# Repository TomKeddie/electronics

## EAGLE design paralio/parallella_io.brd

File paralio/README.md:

# Parallella IO motherboard

# Rev 1.1

## IO Mapping

| Linux GPIO | Zynq Pin | PEC PIN | PEC NAME | Arduino Pin | Local Function |
| ---------- | -------- | ------- | -------- | ----------- | -------------- |

## Issues list
- DFM, need to remove components from underside to reduce cost

# Rev 1.0
## IO Mapping (to be verified)
| Linux GPIO | Zynq Pin | Zynq Name | PEC PIN | PEC NAME | Arduino Pin | Local Function |
| ---- | ---- | ---- | ---- | ---- | ---- | ---- |
| 54 | U17 | IO_L9N_T1_DQS_34             | F3 | GPIO0_N | D7 | - |
| 56 | T16 | IO_L9P_T1_DQS_34             | F5 | GPIO0_P | D6 | -  |
| 1 | W16 | IO_L18N_T2_34                | F4 | GPIO1_N | A0 | LCD_D0 |
| 3 | V16 | IO_L18P_T2_34                | F6 | GPIO1_P | A1 | LCD_D1 |
| 58 | P16 | IO_L24N_T3_34                    | F7 | GPIO2_N | D5 | - |
| 60 | P15 | IO_L24P_T3_34                    | F9 | GPIO2_P | D4 | - |
| 5 | U19 | IO_L12P_T1_MRCC_34               | F8 | GPIO3_N | A2 | LCD_D2 |
| 7 | U18 | IO_L12N_T1_MRCC_34               | F10 | GPIO3_P | A3 | LCD_D3 |
| 62 | R14 | IO_L6N_T0_VREF_34                | F13 | GPIO4_N | D3 | - |
| 64 | P14 | IO_L6P_T0_34                     | F15 | GPIO4_P | D2 | - |
| 9 | T15 | IO_L5N_T0_34                     | F14 | GPIO5_N | A4 | LCD_D4 |
| 11 | T14 | IO_L5P_T0_34                       | F16 | GPIO5_P | A5 | LCD_D5 |
| 66 | U15 | IO_L11N_T1_SRCC_34             | F17 | GPIO6_N | D1/TX | - |
| 68 | U14 | IO_L11P_T1_SRCC_34             | F19 | GPIO6_P | D0/RX | - |
| 13 | W14 | IO_L8N_T1_34                   | F18 | GPIO7_N | - | LCD_D6 |
| 15 | Y14 | IO_L8P_T1_34                   | F20 | GPIO7_P | - | LCD_D7 |
| 16 | V13 | IO_L3N_T0_DQS_34                   | F23 | GPIO8_N | D11 | - |
| 18 | U13 | IO_L3P_T0_DQS_PUDC_B_34 | F25 | GPIO8_P | D10 | LCD_E |
| 17 | W12 | IO_L4N_T0_34            | F24 | GPIO9_N | SDA* | - |
| 19 | V13 | IO_L4P_T0_34             | F26 | GPIO9_P | SCL* | - |
| 20 | U12 | IO_L2N_T0_34             | F27 | GPIO10_N | D9 | LCD_RW |
| 22 | T12 | IO_L2P_T0_34             | F29 | GPIO10_P | D8 | LCD_RS  |
| 21 | T10 | IO_L1N_T0_34             | F28 | GPIO11_N | D13 | - |
| 23 | T11 | IO_L1P_T0_34             | F30 | GPIO11_P | D12 | - |

## Issues list

- Random large vias
- Buttons on same i/o as lcd
- I2C not bidirectional
- wrong package on ULN2803
- connector on parallela hits the led uln2803
- cap beside xilinx jtag clashes with cap on parallela
- shunt and fan connector block access to microsd

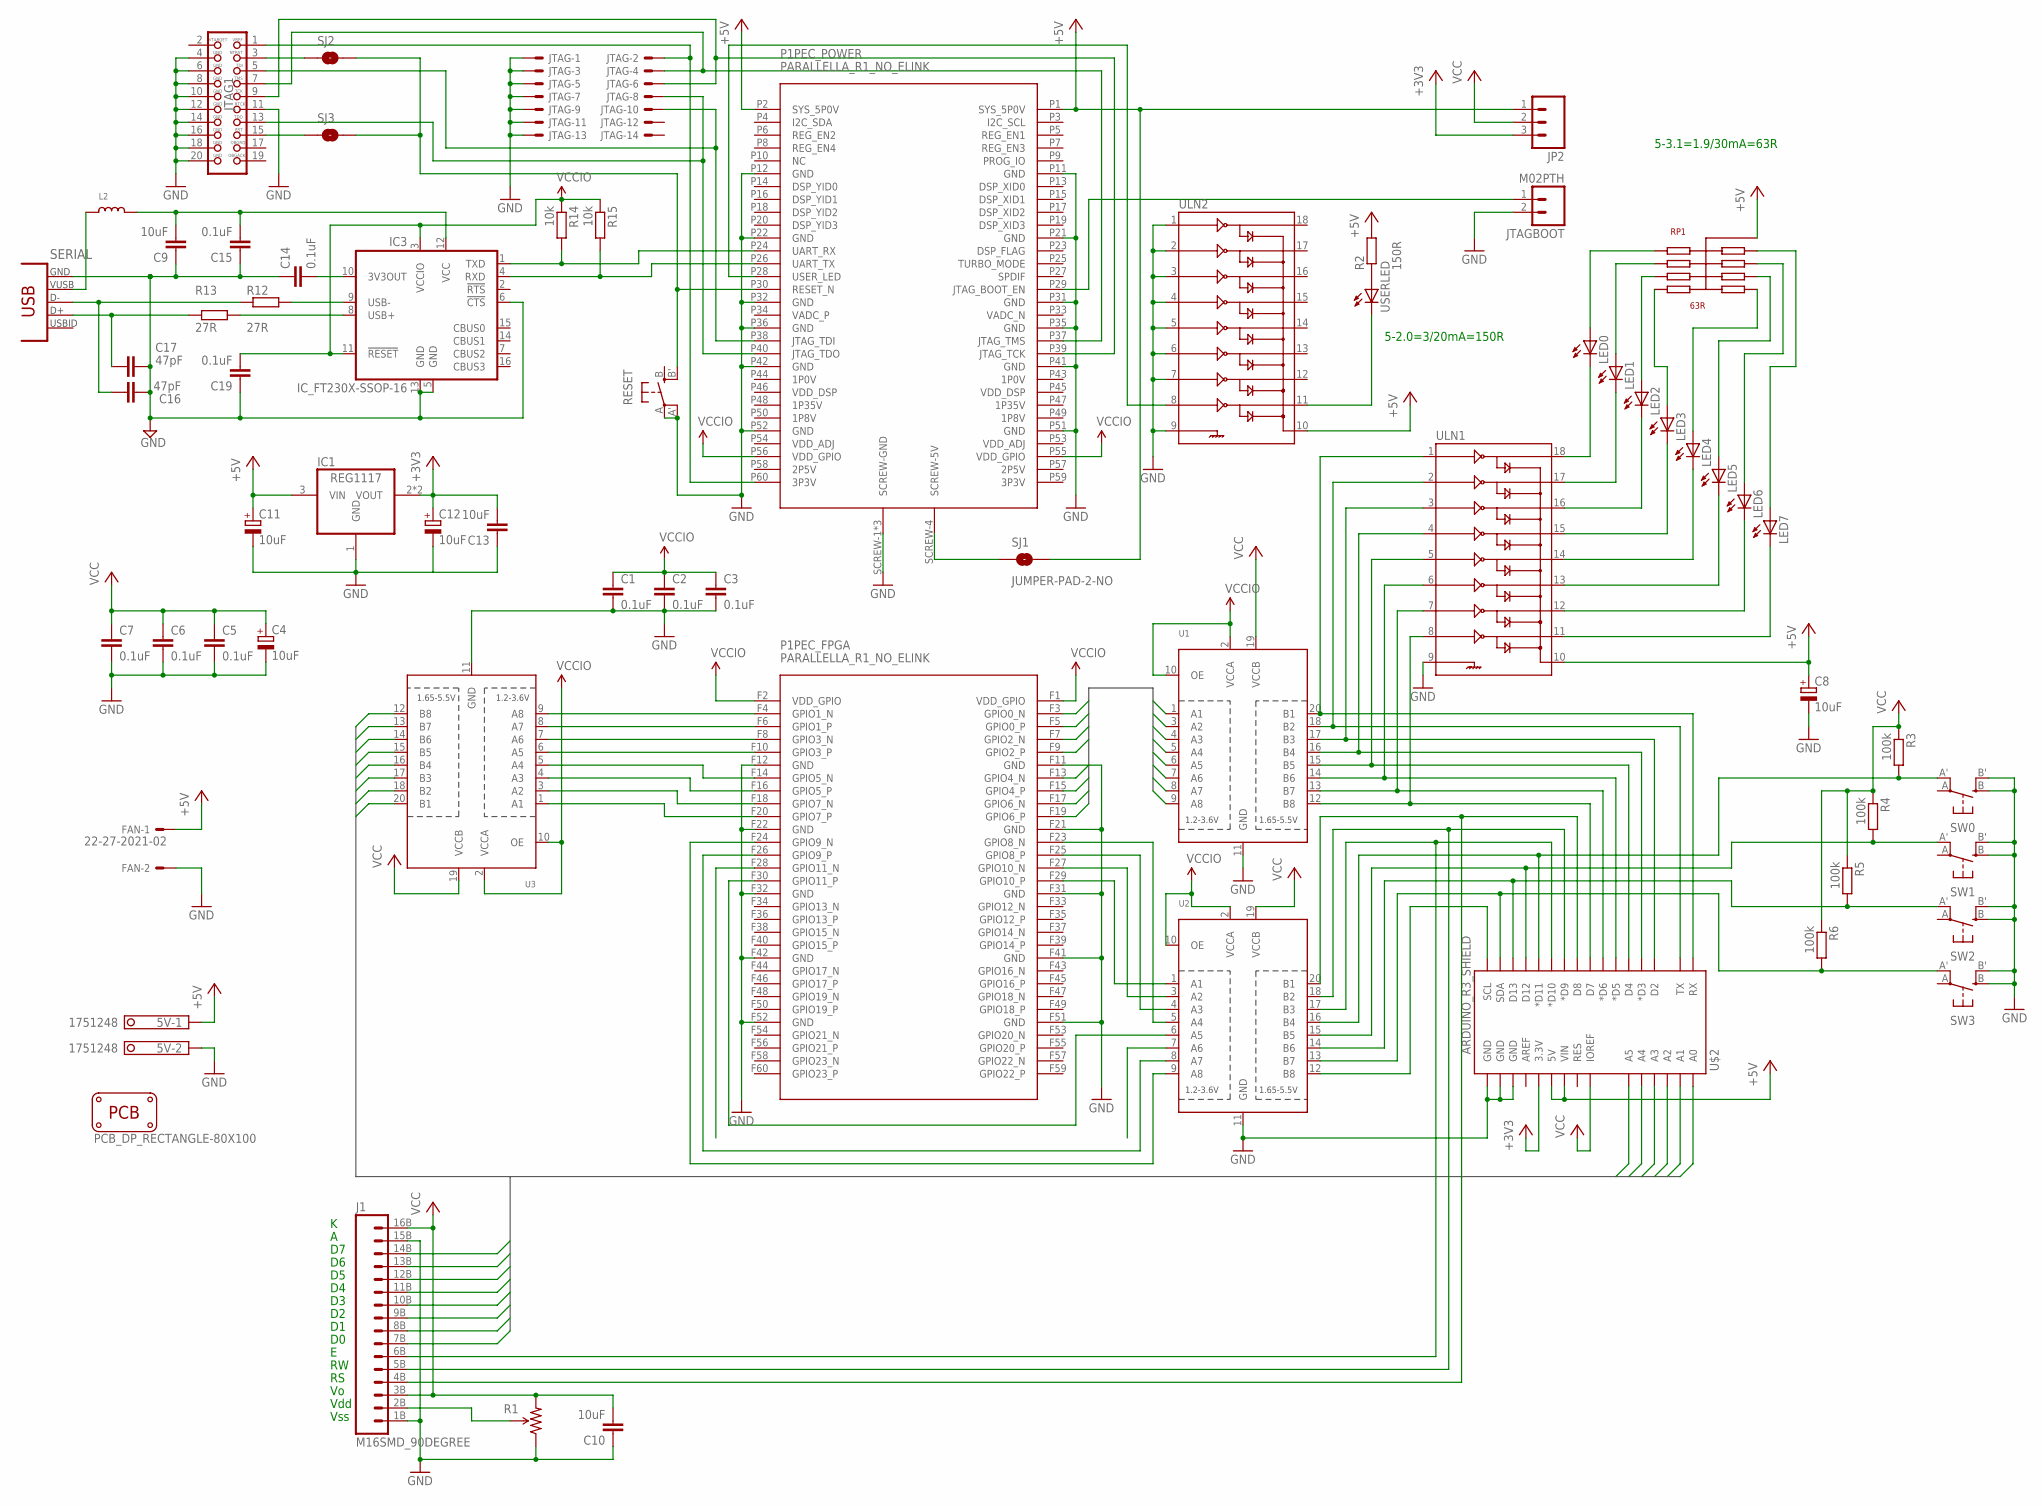
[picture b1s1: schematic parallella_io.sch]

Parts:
5V: 1751248
C1, C2, C3, C5, C6, C7, C14, C15, C19: 0.1uF; C0603-N
C4, C8, C11, C12: 10uF; D/7343-31W
C9, C10, C13: 10uF; C0603-N
C16, C17: 47pF; C0603-N; MOUSER 77-VJ0603A470KXAAC
FAN: 22-27-2021-02; 6410-02
IC1: REG1117; SOT223; MOUSER 701-SPX1117M3-L-33TR
IC3: IC_FT230X-SSOP-16; SSOP-16-FTDI; MOUSER 895-FT230XS-R
J1: M16SMD_90DEGREE; 1X16_SMD_90DEGREE
JP2: M03LONGPADS; 1X03_LONGPADS
JTAG: 87758-1416; MOUSER 538-87833-5320
JTAG1: JTAG-ARM
JTAGBOOT: M02PTH; 1X02
L2: INDUCTOR0805; 0805
LED0, LED1, LED2, LED3, LED4, LED5, LED6, LED7: LED1206; LED-1206
P1: PARALLELLA_R1_NO_ELINK
PCB1: PCB_DP_RECTANGLE-80X100; DP10080_V1
R1: TRIMPOT; TRIMPOT-5MM-V2; MOUSER 72-TS53YL-10K
R2: 150R; R0603-N
R3, R4, R5, R6: 100k; R0603-N
R12, R13: 27R; R0603-N; MOUSER 71-CRCW060327R0JNEB
R14: 10k; R0603-S
R15: 10k; R0603-N
RESET: SPST_TACT-EVQQ2; EVQ-Q2
RP1: 63R; 745C10; MOUSER 774-745C101680JP
SERIAL: CON-USB-F-MINI-B; CONN_USB_MINI-B
SJ1, SJ2, SJ3: JUMPER-PAD-2-NO; PAD-JUMPER-2-NO_NO_SILK
SW0, SW1, SW2, SW3: SPST_TACT-EVQQ2; EVQ-Q2
U1, U2, U3: TXB0108PWR; TSSOP20; MOUSER 595-TXB0108PWR
U$2: ARDUINO_R3_SHIELD; UNO_R3_SHIELD
ULN1, ULN2: ULN2803SOICW; SO18L; MOUSER 595-ULN2803ADWR
USERLED: LED1206; LED-1206

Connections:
3V3OUT: C14.2, IC3.10 (3V3OUT)
+3V3: C12.+, C13.2, IC1.2 (VOUT), IC1.4 (VOUT), JP2.3, U$2.3.3V
+5V: 5V.1, C8.+, C11.+, FAN.1, IC1.3 (VIN), JP2.1, P1.P1 (SYS_5P0V), P1.P2 (SYS_5P0V), R2.2, RP1.1 (COMMON), RP1.6 (COMMON), SJ1.2, U$2.5V, U$2.VIN, ULN1.10, ULN2.10
A0: J1.7B (7), U3.20 (B1), U$2.A0
A1: J1.8B (8), U3.18 (B2), U$2.A1
A2: J1.9B (9), U3.17 (B3), U$2.A2
A3: J1.10B (10), U3.16 (B4), U$2.A3
A4: J1.11B (11), U3.15 (B5), U$2.A4
A5: J1.12B (12), U3.14 (B6), U$2.A5
A6: J1.13B (13), U3.13 (B7)
A7: J1.14B (14), U3.12 (B8)
B0: P1.F19 (GPIO6_P), U1.1 (A1)
B1: P1.F17 (GPIO6_N), U1.3 (A2)
B2: P1.F15 (GPIO4_P), U1.4 (A3)
B3: P1.F13 (GPIO4_N), U1.5 (A4)
B4: P1.F9 (GPIO2_P), U1.6 (A5)
B5: P1.F7 (GPIO2_N), U1.7 (A6)
B6: P1.F5 (GPIO0_P), U1.8 (A7)
B7: P1.F3 (GPIO0_N), U1.9 (A8)
GND: 5V.2, C1.2, C2.2, C3.2, C4.-, C5.2, C6.2, C7.2, C8.-, C9.1, C10.1, C11.-, C12.-, C13.1, C14.1, C15.1, C16.2, C17.2, C19.1, FAN.2, IC1.1 (GND), IC3.5 (GND), IC3.6 (!CTS), IC3.13 (GND), J1.1B (1), J1.15B (15), JTAG.1, JTAG.3, JTAG.5, JTAG.7, JTAG.9, JTAG.11, JTAG.13, JTAG1.4, JTAG1.6, JTAG1.8, JTAG1.10, JTAG1.11, JTAG1.12, JTAG1.14, JTAG1.16, JTAG1.18, JTAG1.20, JTAGBOOT.2, P1.F11 (GND), P1.F12 (GND), P1.F21 (GND), P1.F22 (GND), P1.F31 (GND), P1.F32 (GND), P1.F41 (GND), P1.F42 (GND), P1.F51 (GND), P1.F52 (GND), P1.P11 (GND), P1.P12 (GND), P1.P21 (GND), P1.P22 (GND), P1.P31 (GND), P1.P32 (GND), P1.P35 (GND), P1.P36 (GND), P1.P41 (GND), P1.P42 (GND), P1.P51 (GND), P1.P52 (GND), P1.SCREW-1 (SCREW-GND), P1.SCREW-2 (SCREW-GND), P1.SCREW-3 (SCREW-GND), R1.A (CCW), RESET.A, RESET.A' (P1), SERIAL.GND, SW0.B (S), SW0.B' (S1), SW1.B (S), SW1.B' (S1), SW2.B (S), SW2.B' (S1), SW3.B (S), SW3.B' (S1), U1.11 (GND), U2.11 (GND), U3.11 (GND), U$2.GND@0 (GND), U$2.GND@1 (GND), U$2.GND@2 (GND), ULN1.9, ULN2.1, ULN2.2, ULN2.3, ULN2.4, ULN2.5, ULN2.6, ULN2.7, ULN2.9
unnamed: JTAGBOOT.1, P1.P29 (JTAG_BOOT_EN)
unnamed: P1.F10 (GPIO3_P), U3.6 (A5)
unnamed: P1.F8 (GPIO3_N), U3.7 (A6)
unnamed: P1.F6 (GPIO1_P), U3.8 (A7)
unnamed: P1.F4 (GPIO1_N), U3.9 (A8)
unnamed: JTAG.2, JTAG1.1, P1.P60 (3P3V)
unnamed: JTAG1.3, SJ2.1
unnamed: P1.SCREW-4 (SCREW-5V), SJ1.1
unnamed: P1.F23 (GPIO8_N), U2.5 (A4)
unnamed: P1.F25 (GPIO8_P), U2.4 (A3)
unnamed: P1.F27 (GPIO10_N), U2.3 (A2)
unnamed: P1.F29 (GPIO10_P), U2.1 (A1)
unnamed: P1.F30 (GPIO11_P), U2.6 (A5)
unnamed: P1.F26 (GPIO9_P), U2.8 (A7)
unnamed: P1.F24 (GPIO9_N), U2.9 (A8)
unnamed: R2.1, USERLED.A
unnamed: ULN2.11, USERLED.C
unnamed: P1.P28 (USER_LED), ULN2.8
unnamed: JTAG1.15, SJ3.1
unnamed: P1.F14 (GPIO5_N), U3.5 (A4)
unnamed: P1.F16 (GPIO5_P), U3.4 (A3)
unnamed: P1.F18 (GPIO7_N), U3.3 (A2)
unnamed: P1.F20 (GPIO7_P), U3.1 (A1)
unnamed: U1.16 (B4), U$2.D3 (*D3), ULN1.4
unnamed: U1.15 (B5), U$2.D4, ULN1.5
unnamed: U1.14 (B6), U$2.D5 (*D5), ULN1.6
unnamed: U1.20 (B1), U$2.RX, ULN1.1
unnamed: U1.18 (B2), U$2.TX, ULN1.2
unnamed: U1.17 (B3), U$2.D2, ULN1.3
unnamed: U1.13 (B7), U$2.D6 (*D6), ULN1.7
unnamed: U1.12 (B8), U$2.D7, ULN1.8
unnamed: J1.4B (4), U2.20 (B1), U$2.D8
unnamed: J1.5B (5), U2.18 (B2), U$2.D9 (*D9)
unnamed: J1.6B (6), U2.17 (B3), U$2.D10 (*D10)
unnamed: R3.2, SW0.A' (P1), U2.16 (B4), U$2.D11 (*D11)
unnamed: JTAG.8, JTAG1.13, P1.P40 (JTAG_TDO)
unnamed: R6.2, SW3.A' (P1), U2.13 (B7), U$2.SDA
unnamed: R5.2, SW2.A' (P1), U2.14 (B6), U$2.D13
unnamed: R4.2, SW1.A' (P1), U2.15 (B5), U$2.D12
unnamed: U2.12 (B8), U$2.SCL
unnamed: JTAG.10, JTAG1.5, P1.P38 (JTAG_TDI)
unnamed: JTAG.4, JTAG1.7, P1.P37 (JTAG_TMS)
unnamed: JTAG.6, JTAG1.9, P1.P39 (JTAG_TCK)
unnamed: LED0.A, RP1.10 (R8)
unnamed: LED1.A, RP1.9 (R7)
unnamed: LED2.A, RP1.8 (R6)
unnamed: LED3.A, RP1.7 (R5)
unnamed: LED4.A, RP1.5 (R4)
unnamed: LED0.C, ULN1.18
unnamed: LED1.C, ULN1.17
unnamed: LED2.C, ULN1.16
unnamed: LED3.C, ULN1.15
unnamed: LED4.C, ULN1.14
unnamed: LED5.C, ULN1.13
unnamed: LED6.C, ULN1.12
unnamed: LED7.C, ULN1.11
unnamed: LED5.A, RP1.4 (R3)
unnamed: LED6.A, RP1.3 (R2)
unnamed: LED7.A, RP1.2 (R1)
unnamed: C16.1, R12.1, SERIAL.D-
unnamed: P1.P30 (RESET_N), RESET.B' (S1), SJ2.2, SJ3.2
unnamed: C17.1, R13.1, SERIAL.D+
unnamed: J1.2B (2), R1.B (WIPER)
unnamed: IC3.9 (USB-), R12.2
unnamed: IC3.8 (USB+), R13.2
unnamed: L2.1, SERIAL.VUSB
RXD: IC3.1 (TXD), P1.P24 (UART_RX), R14.2
TXD: IC3.4 (RXD), P1.P26 (UART_TX), R15.2
VCC: C4.+, C5.1, C6.1, C7.1, C10.2, J1.3B (3), J1.16B (16), JP2.2, R1.C (CW), R3.1, R4.1, R5.1, R6.1, U1.19 (VCCB), U2.19 (VCCB), U3.19 (VCCB), U$2.IOREF
VCCIO: C1.1, C2.1, C3.1, C19.2, IC3.3 (VCCIO), IC3.11 (!RESET), P1.F1 (VDD_GPIO), P1.F2 (VDD_GPIO), P1.P55 (VDD_GPIO), P1.P56 (VDD_GPIO), R14.1, R15.1, U1.2 (VCCA), U1.10 (OE), U2.2 (VCCA), U2.10 (OE), U3.2 (VCCA), U3.10 (OE)
VUSB: C9.2, C15.2, IC3.12 (VCC), L2.2

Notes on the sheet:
Vss
Vdd
5-3.1=1.9/30mA=63R
5-2.0=3/20mA=150R

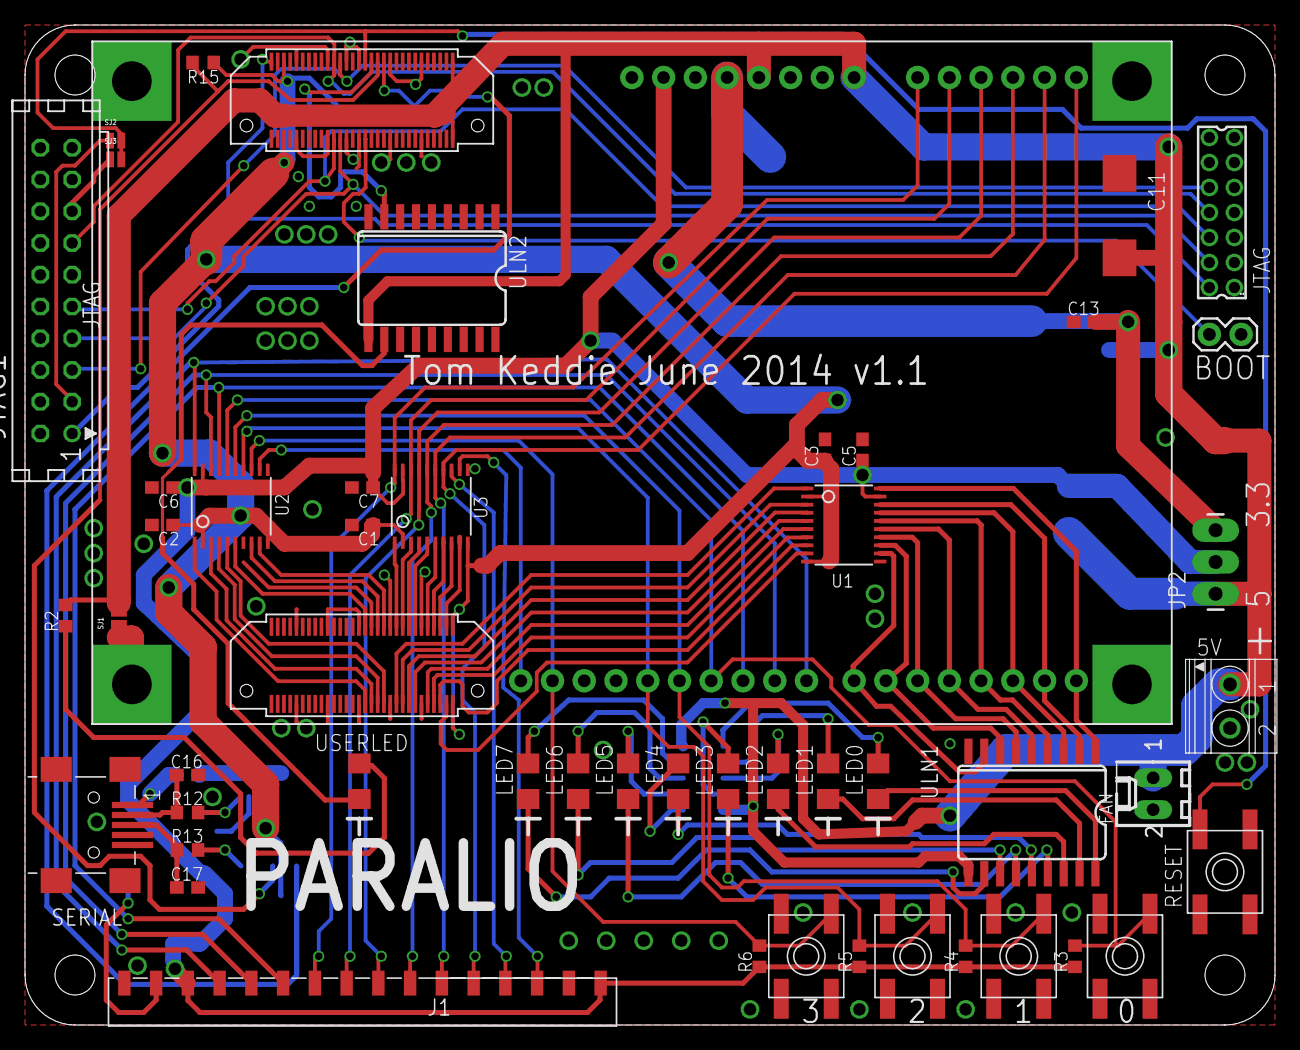
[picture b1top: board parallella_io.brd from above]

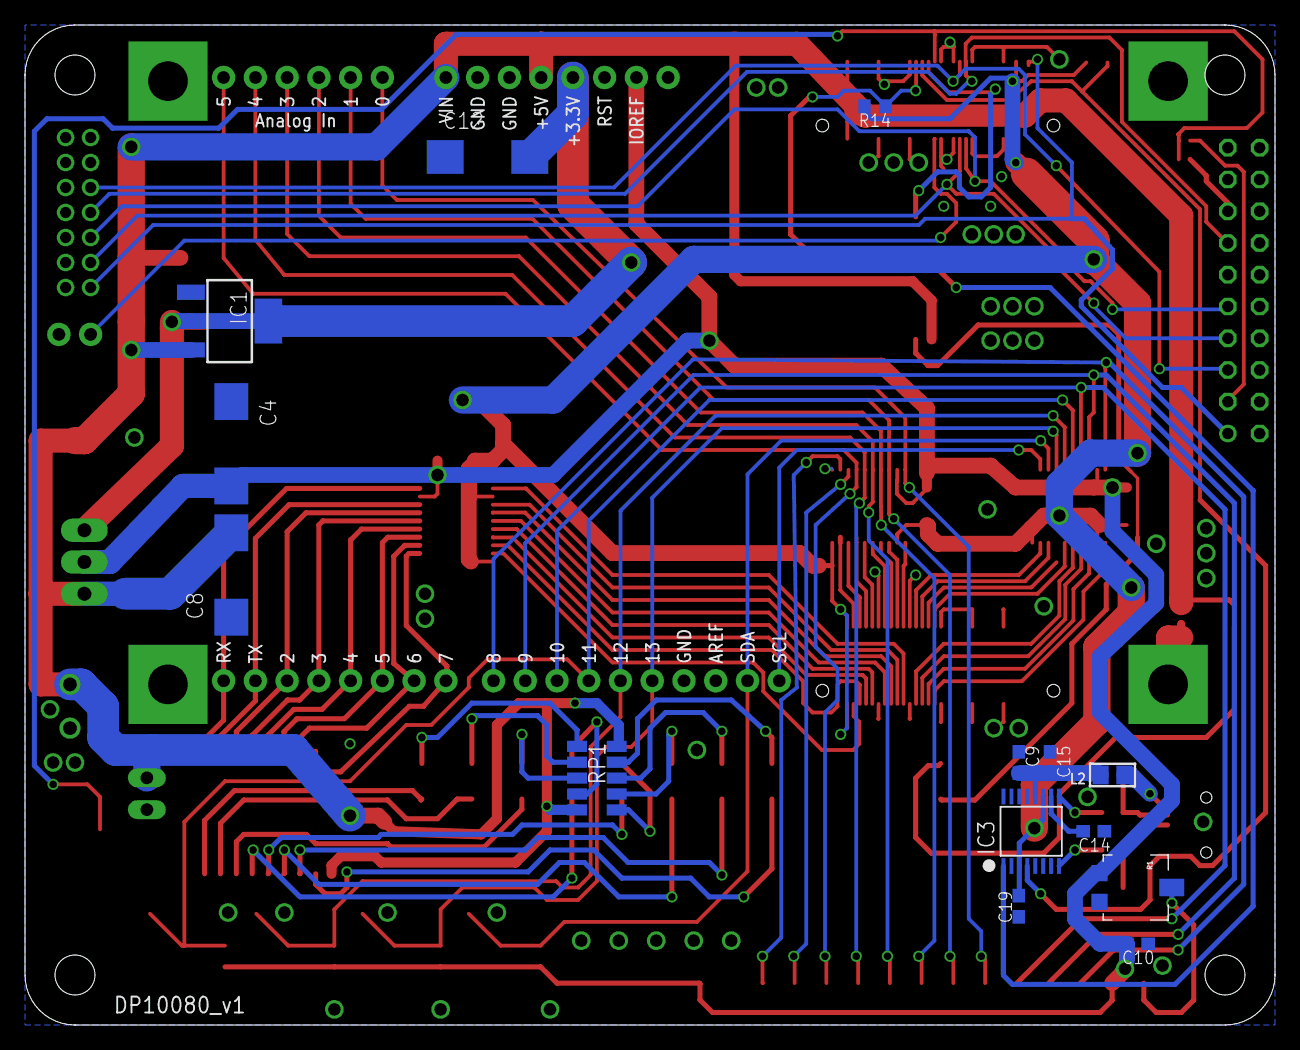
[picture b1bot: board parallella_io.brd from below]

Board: 2 copper layers, 100.0 x 80.0 mm, 65 parts (15 on the bottom side), 91 nets.

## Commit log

2015-06-25 Add paralio 1.0 doco
2015-06-25 Updated paralio readme
2015-07-10 Update README.md
    Add IO Mapping for 1.0 and 1.1
2015-07-10 Update README.md
    Fix tables
2015-07-10 Update README.md
    Test
2015-07-11 Update README.md
    Add linux gpio numbers
2015-07-11 Update README.md
    Fix P/N swap
2015-07-12 Update README.md
    Fix reversal of D0-7
2015-07-12 Update README.md
    Fix D0-D7 GPIOs
2015-07-12 Add LED knight rider
2015-08-13 Added instructions and placement for smd star
2015-08-13 Added animated image
2016-09-18 Added 1.1 of eagle files
2017-03-29 Added paste mask
2017-10-26 Added 1.27mm 2x5 Cortex test clip design
2017-10-26 Add md
2017-10-26 Typo
2017-10-26 Updated md

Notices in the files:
parts and their libraries:
SparkFun-Boards: Licensing: Creative Commons ShareAlike 4.0 International - https://creativecommons.org/licenses/by-sa/4.0
microbuilder: This work is placed in the public domain, and may be freely used for commercial and non-commercial work with the following conditions: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
